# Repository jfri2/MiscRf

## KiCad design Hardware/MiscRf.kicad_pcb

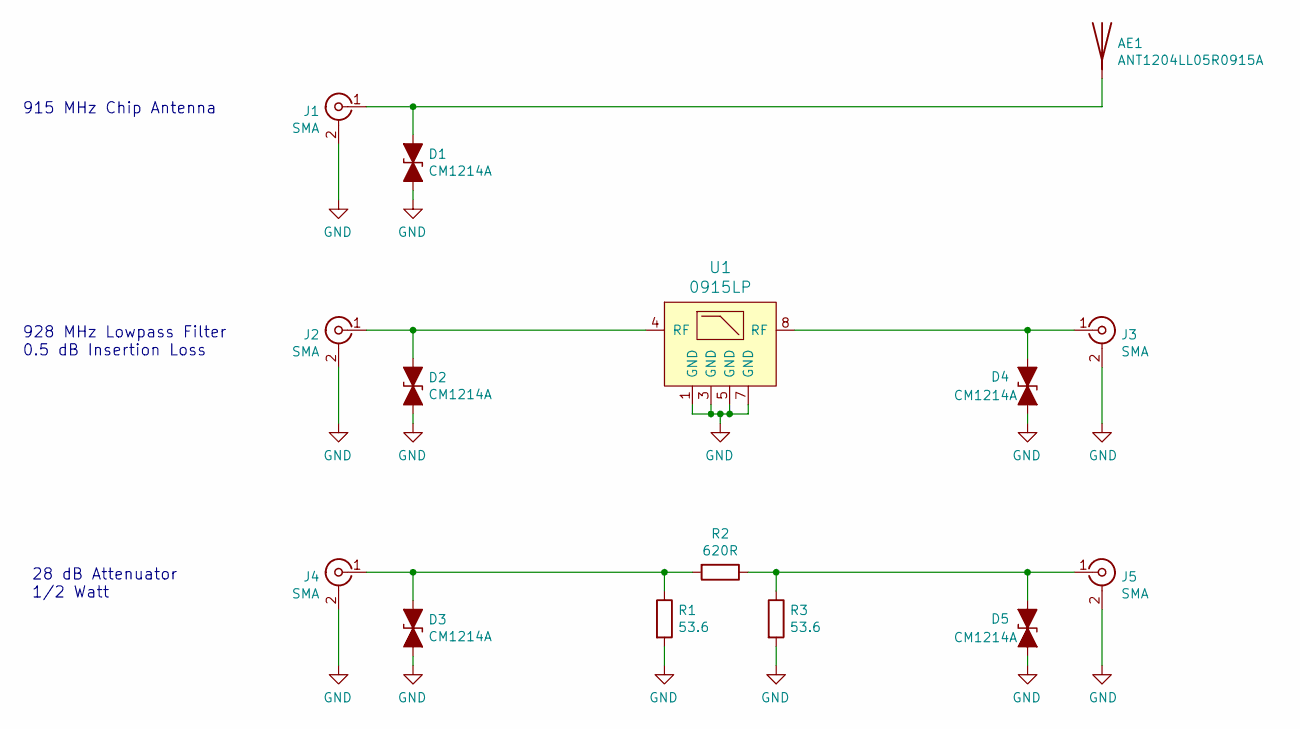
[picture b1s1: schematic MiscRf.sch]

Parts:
AE1: ANT1204LL05R0915A; ANT1204
D1, D2, D3, D4, D5: CM1214A; SOT-23
J1, J2, J3, J4, J5: SMA; J502
R1, R3: 53.6; R_1210
R2: 620R; R_1210
U1: 0915LP

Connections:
GND: D1.2 (A2), D2.2 (A2), D3.2 (A2), D4.2 (A2), D5.2 (A2), J1.2 (Ext), J2.2 (Ext), J3.2 (Ext), J4.2 (Ext), J5.2 (Ext), R1.2, R3.2, U1.1 (GND), U1.3 (GND), U1.5 (GND), U1.7 (GND)
unnamed: AE1.1, D1.1 (A1), J1.1 (In)
unnamed: D2.1 (A1), J2.1 (In), U1.4 (RF)
unnamed: D3.1 (A1), J4.1 (In), R1.1, R2.2
unnamed: D4.1 (A1), J3.1 (In), U1.8 (RF)
unnamed: D5.1 (A1), J5.1 (In), R2.1, R3.1

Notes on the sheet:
28 dB Attenuator 1/2 Watt
928 MHz Lowpass Filter 0.5 dB Insertion Loss
915 MHz Chip Antenna

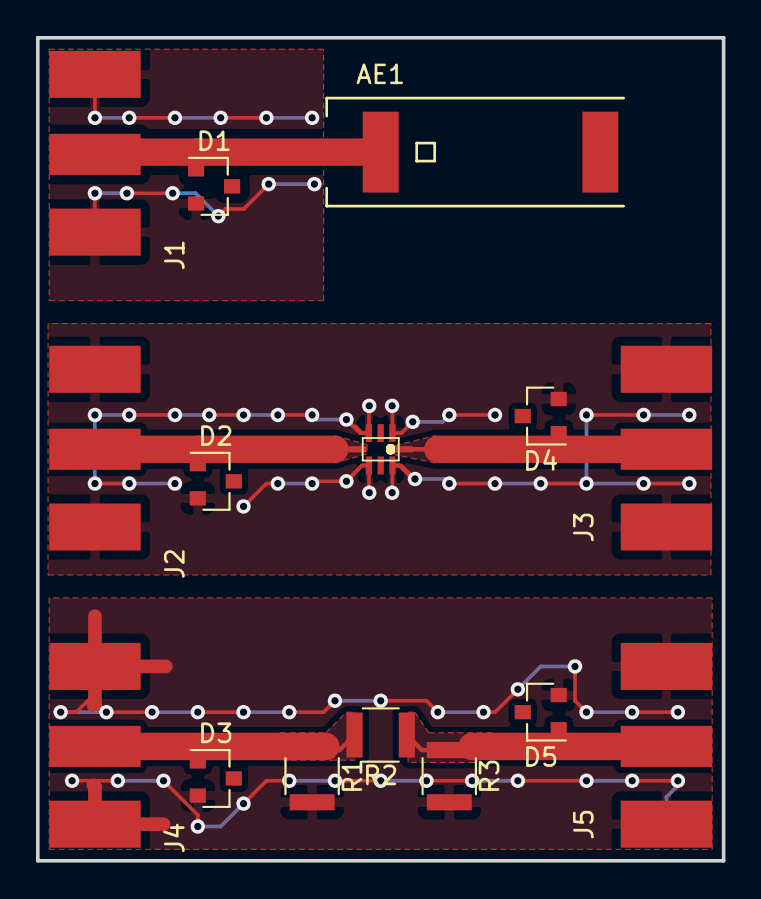
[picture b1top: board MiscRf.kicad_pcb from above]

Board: 2 copper layers, 38.1 x 45.7 mm, 15 parts (0 on the bottom side), 6 nets.

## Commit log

2017-08-15 Generated PDFs of schematic and layout
2017-08-15 Generated Gerbers
